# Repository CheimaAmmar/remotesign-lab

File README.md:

# RemoteSignLab

RemoteSignLab is an academic prototype for **secure remote electronic signatures** combining a hardware authentication terminal, a FastAPI backend, PKCS#11-based key protection, PAdES PDF signatures, RFC 3161 timestamps, and tamper-evident security auditing.

The system uses an **ESP32-C3 terminal with RFID and fingerprint authentication** to authorize signing requests, while the RSA signing key remains protected on the server side through **SoftHSM2 and PKCS#11**.

The project also includes a custom PCB designed with KiCad and manufactured locally using an **Emblaser 2 laser-assisted resist process followed by chemical etching**.

---

## Project Highlights

### Secure remote signing

- PAdES-B-B and PAdES-B-T PDF signatures
- RSA signing through PKCS#11
- SoftHSM2-protected signing key
- RFC 3161 timestamp authority integration
- Signed PDF integrity and signature verification

### Strong user authentication

- ESP32-C3 authentication terminal
- MFRC522 RFID reader
- DY50 fingerprint sensor
- SSD1306 OLED display
- Explicit user consent before signature authorization

### Device security

- HMAC-SHA256 authenticated requests
- Timestamp validation
- Persistent nonce anti-replay protection
- Device, document and approval-context binding
- HTTPS with server certificate validation

### Backend and audit

- FastAPI
- PostgreSQL
- Separate USER and ADMIN interfaces
- Signature-request queue
- Structured security audit events
- SHA-256 tamper-evident audit hash chain
- PostgreSQL advisory-lock serialization
- ADMIN audit filtering, pagination and CSV export
- Audit-chain integrity verification

### Hardware development

- Custom KiCad schematic
- Custom PCB routing
- ESP32-C3 / RFID / fingerprint / OLED integration
- Emblaser 2 laser engraving
- Chemical PCB etching
- Manual drilling, soldering and testing

---

# System Architecture

```mermaid
flowchart TD
    User[USER Web Interface] -->|HTTPS| API[FastAPI Backend]
    Admin[ADMIN Web Interface] -->|HTTPS| API

    Device[ESP32-C3 Terminal<br/>RFID + Fingerprint + OLED]
        -->|HTTPS + HMAC-SHA256| API

    API --> DB[(PostgreSQL)]
    API --> HSM[SoftHSM2 / PKCS#11]
    API --> TSA[RFC 3161 TSA]

    HSM --> PDF[PAdES Signed PDF]
    TSA --> PDF
    API --> PDF
```

The FastAPI backend coordinates authentication, authorization, user consent, document management, signature requests, signing and verification.

PostgreSQL stores application and workflow data, including users, devices, documents, authentication sessions, nonces, signature requests, signature metadata and security audit events.

The ESP32-C3 terminal performs the local authentication steps and authenticates sensitive requests to the backend using HMAC-SHA256.

The private RSA signing key is never stored on the ESP32-C3. It remains protected behind the PKCS#11 interface provided by SoftHSM2.

pyHanko generates and validates the PAdES signatures. For PAdES-B-T, an RFC 3161 TSA provides the signature timestamp.

---

# End-to-End Signature Flow

1. The USER signs in to the Web interface.
2. The USER opens an assigned PDF document.
3. The USER explicitly accepts the consent conditions.
4. RemoteSignLab creates a signature request.
5. The ESP32-C3 retrieves the pending request.
6. The terminal verifies the RFID card.
7. The terminal verifies the fingerprint.
8. The backend issues an authentication challenge.
9. Device requests are authenticated using HMAC-SHA256.
10. Timestamp and persistent nonce checks protect against replay attacks.
11. The backend validates the device, document, hash and approval context.
12. The signature request becomes authorized.
13. SoftHSM2 performs the RSA operation through PKCS#11.
14. pyHanko generates the PAdES signature.
15. The RFC 3161 TSA provides a timestamp for PAdES-B-T.
16. The signed PDF becomes available to the USER.
17. Security-sensitive operations are recorded in the audit trail.

No credential, device secret, HSM PIN or private key is stored in this README or intentionally committed to the repository.

---

# Hardware Prototype

RemoteSignLab includes a dedicated authentication terminal based on the **DFRobot Beetle ESP32-C3**.

## Main Components

| Component | Purpose |
| --- | --- |
| DFRobot Beetle ESP32-C3 | Main embedded controller |
| MFRC522 | RFID authentication |
| DY50 | Fingerprint authentication |
| SSD1306 0.96" OLED | Local status and workflow display |
| Custom PCB | Electrical integration of the terminal |

The terminal performs the local authentication operations required before the backend can authorize a remote electronic signature.

## Prototype

The prototype combines the ESP32-C3, RFID reader, fingerprint sensor and OLED display on a custom PCB.

---

# PCB Design

The PCB was designed with **KiCad**.

Editable design files are available in:

[`hardware/kicad/`](hardware/kicad/)

## KiCad Files

- [Electronic schematic](hardware/kicad/remotesign_lab.kicad_sch)
- [PCB layout](hardware/kicad/remotesign_lab.kicad_pcb)

---

## Electronic Schematic

The schematic integrates:

- ESP32-C3
- MFRC522 RFID reader
- DY50 fingerprint sensor
- SSD1306 OLED display
- Power distribution
- SPI communication
- UART communication
- I2C communication

### Schematic Preview

The complete exported schematic is also available as PDF:

[View schematic PDF](hardware/fabrication/schematic.pdf)

---

## PCB Routing

The PCB routing was designed specifically for local prototype fabrication.

### Routing Preview

The editable KiCad PCB file is available here:

[Open the PCB layout](hardware/kicad/remotesign_lab.kicad_pcb)

---

# PCB Fabrication

The PCB was fabricated locally rather than ordered from an industrial PCB manufacturer.

The manufacturing process combines:

- KiCad PCB design
- Copper-layer export
- Black-and-white image processing
- Pattern inversion
- Black resist coating
- Emblaser 2 laser engraving
- Chemical copper etching
- Manual drilling
- Component soldering
- Electrical continuity testing
- Functional testing

## Fabrication Workflow

1. Create the electronic schematic in KiCad.
2. Assign footprints to all components.
3. Place and route the PCB.
4. Export the copper layer.
5. Convert the layout to a high-contrast black-and-white image.
6. Invert the copper pattern for the resist-removal process.
7. Coat the copper-clad board with black paint.
8. Allow the coating to dry.
9. Position and focus the board in the Emblaser 2.
10. Laser-engrave the inverted PCB pattern.
11. Remove the resist from the areas where copper must be etched.
12. Place the board in the chemical etching solution.
13. Remove the exposed unwanted copper.
14. Clean the remaining resist.
15. Drill the pads and component holes.
16. Inspect track continuity.
17. Solder the electronic components.
18. Perform electrical and functional tests.

---

## Laser Engraving Pattern

The copper layout is inverted before laser engraving because the black coating acts as a temporary chemical-etching resist.

The Emblaser 2 removes the coating only from the areas where copper must later be removed by the etchant.

The fabrication pattern is available here:

[View inverted copper layout](hardware/fabrication/copper-layout-inverted.pdf)

---

## After Laser Engraving

At this stage, the laser has selectively removed the black resist coating.

The exposed copper areas will be removed during chemical etching.

---

## After Chemical Etching

After chemical etching, the unwanted copper has been removed.

The remaining copper protected by the resist forms the conductive PCB tracks.

The board can then be cleaned, drilled, assembled and electrically tested.

---

# Hardware Files

```text
hardware/
├── kicad/
│   ├── remotesign_lab.kicad_sch
│   └── remotesign_lab.kicad_pcb
│
└── fabrication/
    ├── schematic.pdf
    └── copper-layout-inverted.pdf
```

Hardware images are stored under:

```text
docs/images/
├── prototype/
│   └── prototype-complete.jpg
│
└── pcb/
    ├── schematic.png
    ├── pcb-routing.png
    ├── pcb-after-laser.jpg
    └── pcb-after-etching.jpg
```

---

# Repository Structure

| Path | Purpose |
| --- | --- |
| `app/` | FastAPI backend, APIs, Web interfaces, security modules and services |
| `alembic/` | PostgreSQL database migrations |
| `firmware/remotesign_lab/` | ESP32-C3 firmware and safe configuration templates |
| `hardware/kicad/` | Editable KiCad schematic and PCB layout |
| `hardware/fabrication/` | PCB fabrication exports and laser patterns |
| `docs/images/` | Hardware prototype and PCB images |
| `docs/` | PAdES, TSA, certificate and audit documentation |
| `scripts/` | Development utilities, certificate tools and development TSA |
| `tests/` | Automated test suite |
| `softhsm/` | Safe SoftHSM configuration; runtime tokens are excluded |

---

# Software Requirements

- Python 3
- PostgreSQL
- SoftHSM2
- PKCS#11 module
- OpenSSL
- ESP32-C3 Arduino-compatible development environment
- KiCad

Pinned Python dependencies are listed in:

[`requirements.txt`](requirements.txt)

---

# Installation

## Python Environment

```bash
python3 -m venv .venv
source .venv/bin/activate
pip install -r requirements.txt
```

## Application Configuration

Create a local configuration file:

```bash
cp .env.example .env
```

Replace all placeholders in `.env` with appropriate local values.

The `.env` file must never be committed.

---

# Database

Apply the database migrations:

```bash
alembic upgrade head
```

The current audit-hardening migration is:

```text
a84f2c1d9e70
```

---

# Running RemoteSignLab

## Backend

Start the FastAPI backend over HTTPS:

```bash
uvicorn app.main:app \
  --host 0.0.0.0 \
  --port 8443 \
  --ssl-keyfile certs/server.key \
  --ssl-certfile certs/server.crt
```

TLS private keys are local files and must remain outside version control.

---

## Development RFC 3161 TSA

For local PAdES-B-T development:

```bash
python -m scripts.dev_tsa_server \
  --config scripts/dev-tsa-openssl.cnf \
  --bind 127.0.0.1 \
  --port 8090
```

The development TSA and its certificates are intended only for testing and demonstration.

They are not a production PKI.

---

# Firmware Configuration

Firmware credentials and the local HTTPS trust anchor are intentionally excluded from Git.

Create them from the safe templates:

```bash
cp firmware/remotesign_lab/secrets.example.h \
   firmware/remotesign_lab/secrets.h

cp firmware/remotesign_lab/trust_anchor.example.h \
   firmware/remotesign_lab/trust_anchor.h
```

Local Wi-Fi credentials and the device authentication secret must only be stored in:

```text
firmware/remotesign_lab/secrets.h
```

The local CA certificate used to validate the HTTPS server belongs in:

```text
firmware/remotesign_lab/trust_anchor.h
```

Both files are excluded from version control.

TLS certificate validation remains enabled through:

```cpp
secureClient.setCACert(SERVER_CA_CERT);
```

The firmware must not use:

```cpp
setInsecure();
```

---

# Security Architecture

RemoteSignLab applies security controls at the device, communication, backend, signing and auditing layers.

## Device Authentication

Sensitive ESP32-C3 requests are protected using:

- HMAC-SHA256
- Timestamp validation
- Random nonces
- Persistent nonce replay detection
- Device identity binding
- Document identity binding
- Document hash binding
- Explicit approval context

---

## Multi-Factor Authentication

The hardware terminal combines:

- RFID authentication
- Fingerprint authentication

Both checks are required before the remote signing workflow can proceed.

---

## Signing Key Protection

The private RSA signing key:

- Is never stored on the ESP32-C3
- Is never embedded in the application source code
- Is accessed through PKCS#11
- Is protected by SoftHSM2 in the prototype environment

---

## TLS

Communication between the ESP32-C3 and FastAPI backend uses HTTPS with server certificate validation.

No insecure TLS fallback is used.

---

## Anti-Replay Protection

Device requests include:

- Timestamps
- Random nonces

Used nonces are persisted to prevent replay across application restarts.

---

# PAdES Signatures

RemoteSignLab supports two PAdES profiles.

## PAdES-B-B

Provides the cryptographic PDF signature and signer certificate information.

## PAdES-B-T

Extends the signature with an RFC 3161 timestamp token.

Future visible PDF signatures include:

```text
ELECTRONICALLY SIGNED
RemoteSignLab

Signer
Certificate
Profile
Date
Signature ID
```

Existing signed PDFs are never modified.

---

# Security Audit Trail

Security-sensitive operations are recorded in a structured audit trail.

The audit system includes:

- Event categories
- Actor identification
- User, device, document, request and signature correlation
- Technical failure codes
- Sensitive-data sanitization
- HTTP request context
- SHA-256 hash chaining
- PostgreSQL advisory locking
- Integrity verification
- ADMIN-only access
- Filtering and pagination
- CSV export

---

## Tamper-Evident Audit Chain

New audit events contain:

```text
previous_hash
event_hash
```

The hash chain provides evidence of database-event modification.

Audit writes are serialized through a PostgreSQL transaction-level advisory lock to prevent concurrent events from referencing the same previous hash.

Historical events created before hash chaining remain unsealed and are not artificially modified.

The integrity checker recalculates the chain in read-only mode.

> The audit hash chain provides tamper evidence, not absolute immutability against an administrator with unrestricted database access.

---

# Sensitive Data Policy

The following data must never be committed:

- `.env`
- Wi-Fi credentials
- `DEVICE_SECRET`
- `secrets.h`
- `trust_anchor.h`
- SoftHSM PINs
- SoftHSM runtime tokens
- Private TLS keys
- Private CA keys
- Private TSA keys
- Private signing keys
- Authentication tokens
- Session tokens
- CSRF tokens
- Administrative secrets

Only safe templates are included in the repository.

---

# Testing

## Compile

```bash
python -m compileall app scripts
```

## Automated Tests

```bash
pytest
```

Current validated baseline:

```text
143 tests passing
```

## Dependency Consistency

```bash
pip check
```

## Dependency Security Audit

```bash
pip-audit -r requirements.txt
```

## Static Security Analysis

```bash
bandit -r app scripts -x tests
```

## Git Consistency

```bash
git diff --check
```

---

# Security Validation Status

Current validated baseline:

| Check | Result |
| --- | --- |
| Automated tests | 143 passed |
| `pip check` | No broken requirements |
| `pip-audit` | No known vulnerabilities |
| Bandit High | 0 |
| Bandit Medium | 0 |
| Bandit Low | 2 |
| Git whitespace check | Passed |

The two remaining Low-severity Bandit findings are associated with the local development TSA invoking OpenSSL through Python `subprocess` without shell execution.

---

# Stable Milestones

The repository includes the following stable development tags:

- `pades-bt-stable`
- `audit-hardening-stable`

---

# Technical Documentation

- [PAdES implementation](docs/pades.md)
- [Development signing certificate](docs/pades-test-certificate.md)
- [Development RFC 3161 TSA](docs/pades-test-tsa.md)
- [Audit trail and hash chain](docs/audit.md)

---

# Project Scope

RemoteSignLab demonstrates a complete academic remote-signature workflow covering:

- Web application development
- Embedded systems
- Multi-factor authentication
- Secure device-to-server communication
- HMAC-based device authentication
- Anti-replay mechanisms
- PKCS#11
- SoftHSM2
- RSA signatures
- PAdES
- RFC 3161 timestamping
- Security audit logging
- Tamper-evident audit chains
- KiCad schematic design
- PCB routing
- PCB prototyping
- Laser engraving
- Chemical etching

---

# Disclaimer

RemoteSignLab is an **academic and demonstration prototype**.

Its development certificates, development TSA, SoftHSM2 configuration, locally manufactured PCB and trust model must not be considered equivalent to:

- A production PKI
- A certified hardware security module
- A qualified trust service provider
- A qualified electronic-signature service

A production deployment would require additional controls such as secure hardware key storage, hardened provisioning, production PKI, device lifecycle management, operational monitoring, high-availability infrastructure and the appropriate regulatory and certification framework.

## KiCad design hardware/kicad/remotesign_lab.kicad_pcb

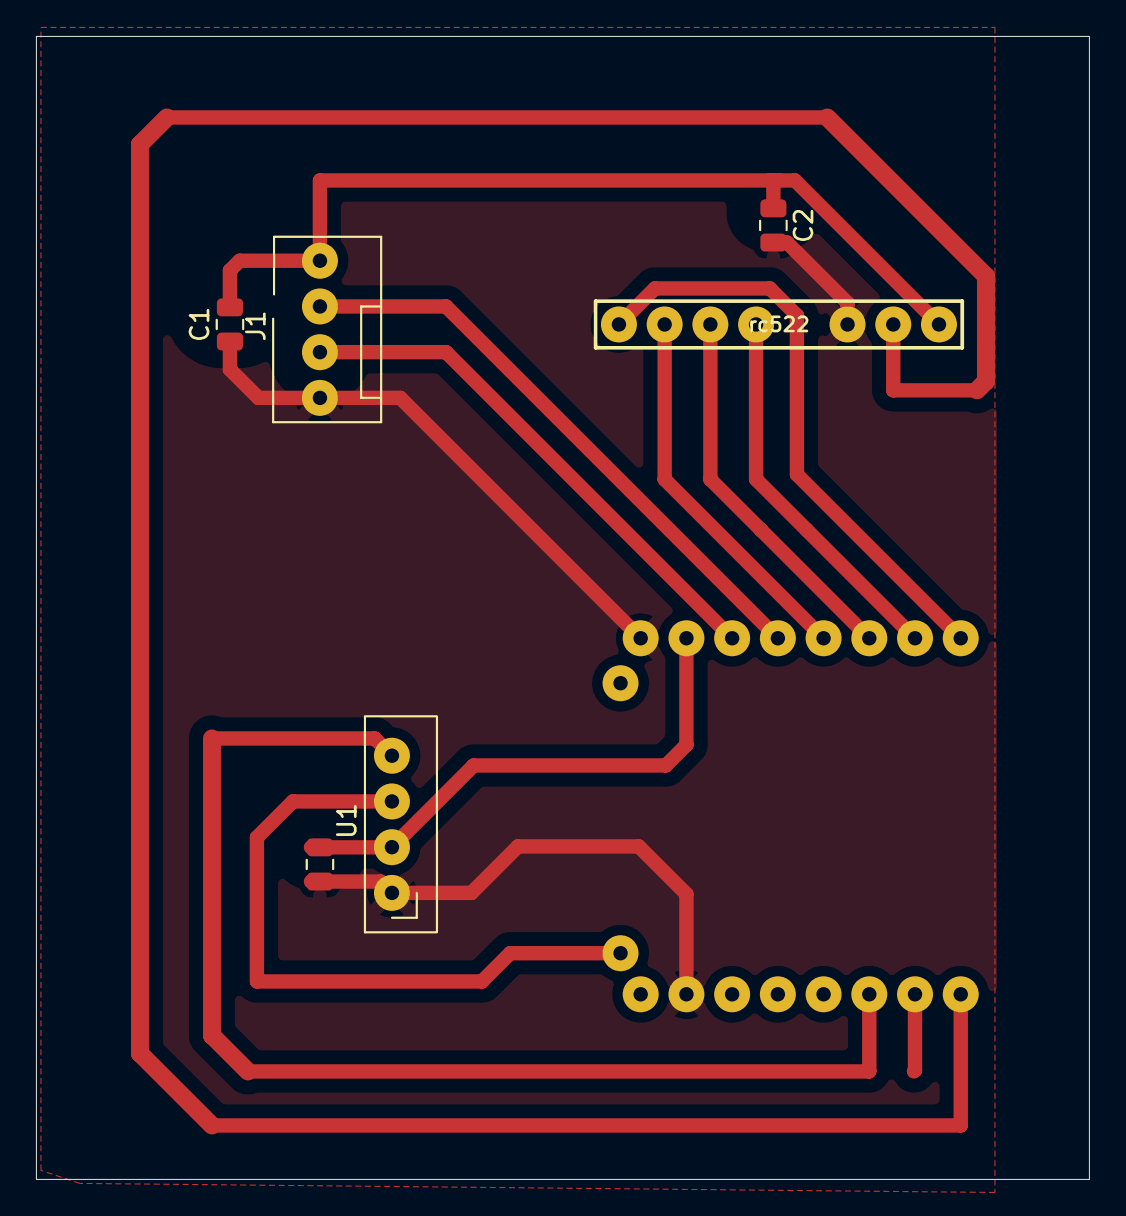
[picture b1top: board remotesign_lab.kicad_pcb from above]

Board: 2 copper layers, 58.5 x 63.5 mm, 7 parts (0 on the bottom side), 11 nets.

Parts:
C1, C2, C3: 100nF; C_0805_2012Metric
J1: Conn_01x04; FanPinHeader_1x04_P2.54mm_Vertical
U1: ER_OLEDM0.91_1x-I2C
U2: BEETLE_ESP32_C3_DFR0868
rc522: RFID-RC522

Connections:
+3V3: C1.2, C2.1, C3.1, J1.4, U1.2 (VCC), U2.2 (3V3), rc522.8 (3V3)
GND: C1.1, C2.2, C3.2, J1.1, U1.1 (GND), U2.1 (GND), U2.15 (GND), rc522.6 (GND)
unnamed: J1.2, U2.3 (GPIO0)
unnamed: J1.3, U2.4 (GPIO1)
unnamed: U1.3 (SCL), U2.17 (GPIO3)
unnamed: U1.4 (SDA), U2.11 (GPIO8_SDA)
unnamed: U2.9 (GPIO2), rc522.7 (RST)
unnamed: U2.5 (GPIO4), rc522.2 (SCK)
unnamed: U2.7 (GPIO5), rc522.4 (MISO)
unnamed: U2.6 (GPIO6), rc522.3 (MOSI)
unnamed: U2.8 (GPIO7), rc522.1 (SDA)
